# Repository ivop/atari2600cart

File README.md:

# atari2600cart
2K/4K Atari 2600 Cartridge PCB

Rescued my 2017 design from backup :)

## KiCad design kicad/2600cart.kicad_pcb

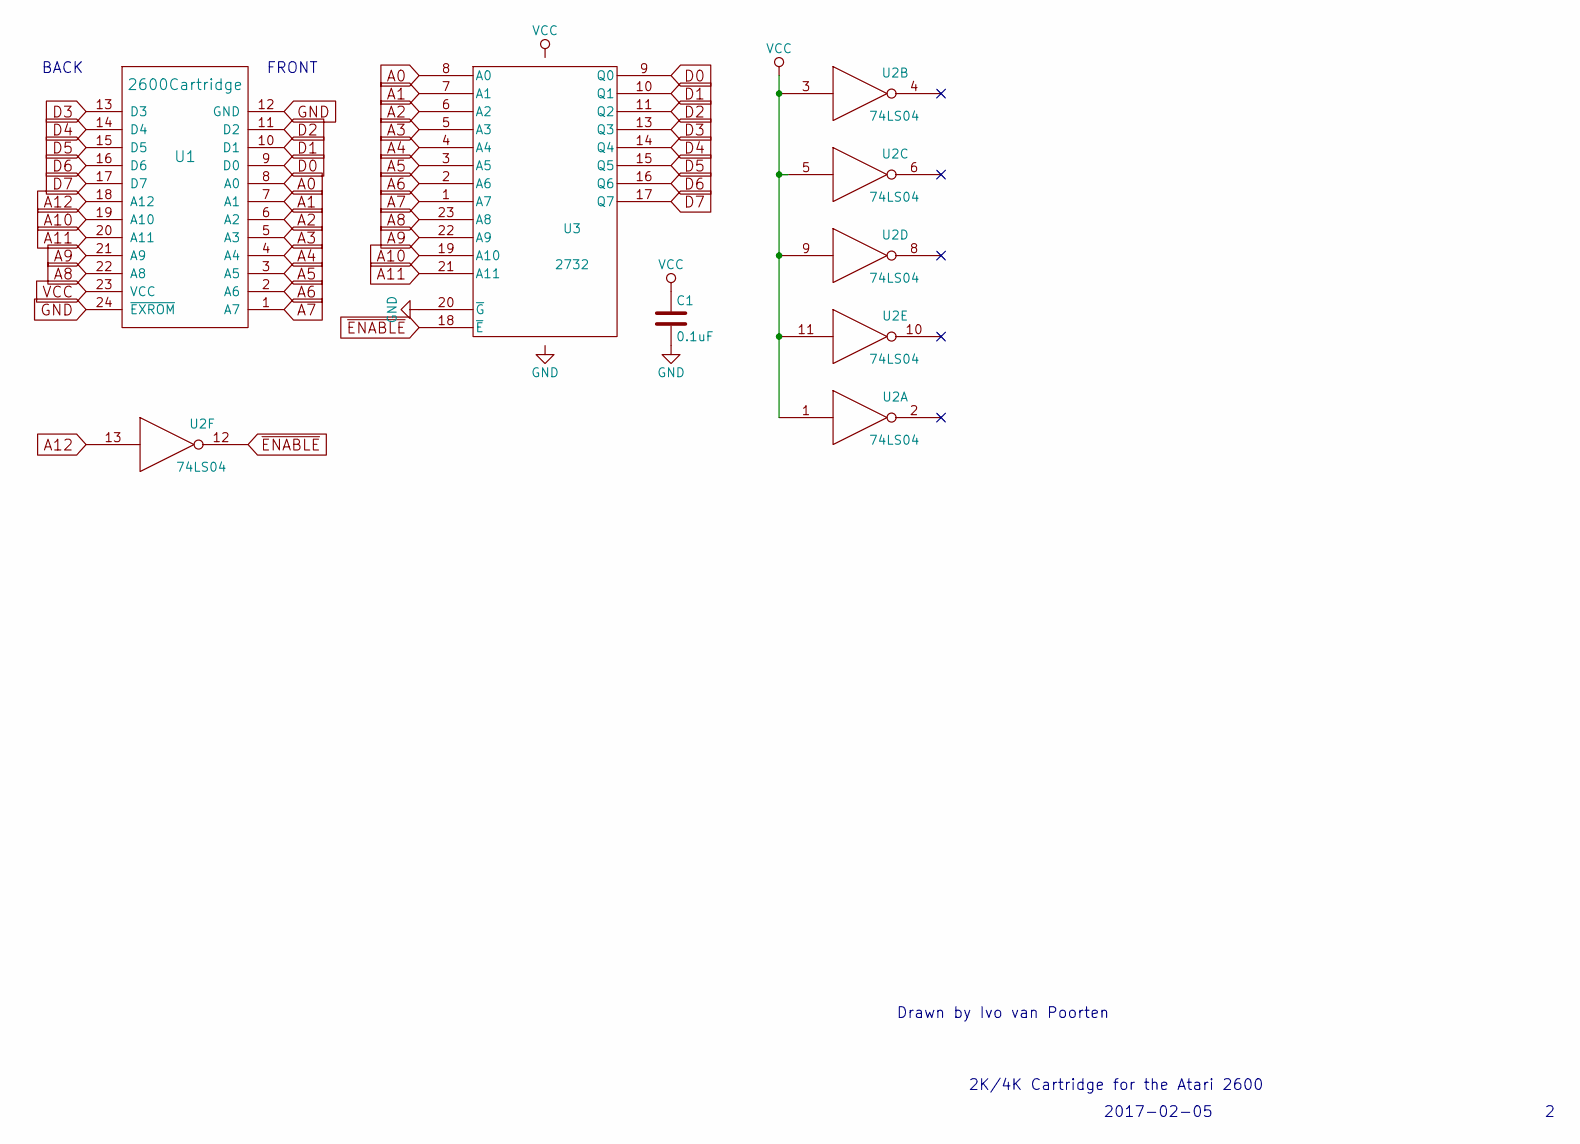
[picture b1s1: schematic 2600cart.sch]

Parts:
C1: 0.1uF; C_Disc_D3.0mm_W2.0mm_P2.50mm
U1: 2600Cartridge; 2600CART
U2: 74LS04; DIP-14_W7.62mm
U3: 2732; DIP-24_W15.24mm

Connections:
A0: U1.8 (A0), U3.8 (A0)
A1: U1.7 (A1), U3.7 (A1)
A2: U1.6 (A2), U3.6 (A2)
A3: U1.5 (A3), U3.5 (A3)
A4: U1.4 (A4), U3.4 (A4)
A5: U1.3 (A5), U3.3 (A5)
A6: U1.2 (A6), U3.2 (A6)
A7: U1.1 (A7), U3.1 (A7)
A8: U1.22 (A8), U3.23 (A8)
A9: U1.21 (A9), U3.22 (A9)
A10: U1.19 (A10), U3.19 (A10)
A11: U1.20 (A11), U3.21 (A11)
A12: U1.18 (A12), U2.13
D0: U1.9 (D0), U3.9 (Q0)
D1: U1.10 (D1), U3.10 (Q1)
D2: U1.11 (D2), U3.11 (Q2)
D3: U1.13 (D3), U3.13 (Q3)
D4: U1.14 (D4), U3.14 (Q4)
D5: U1.15 (D5), U3.15 (Q5)
D6: U1.16 (D6), U3.16 (Q6)
D7: U1.17 (D7), U3.17 (Q7)
GND: C1.2, U1.12 (GND), U1.24 (~EXROM), U2.7 (GND), U3.12 (GND), U3.20 (~G)
VCC: C1.1, U1.23 (VCC), U2.1, U2.3, U2.5, U2.9, U2.11, U2.14 (VCC), U3.24 (Vcc)
~ENABLE: U2.12, U3.18 (~E)

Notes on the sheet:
2K/4K Cartridge for the Atari 2600
2017-02-05
Drawn by Ivo van Poorten
FRONT
BACK

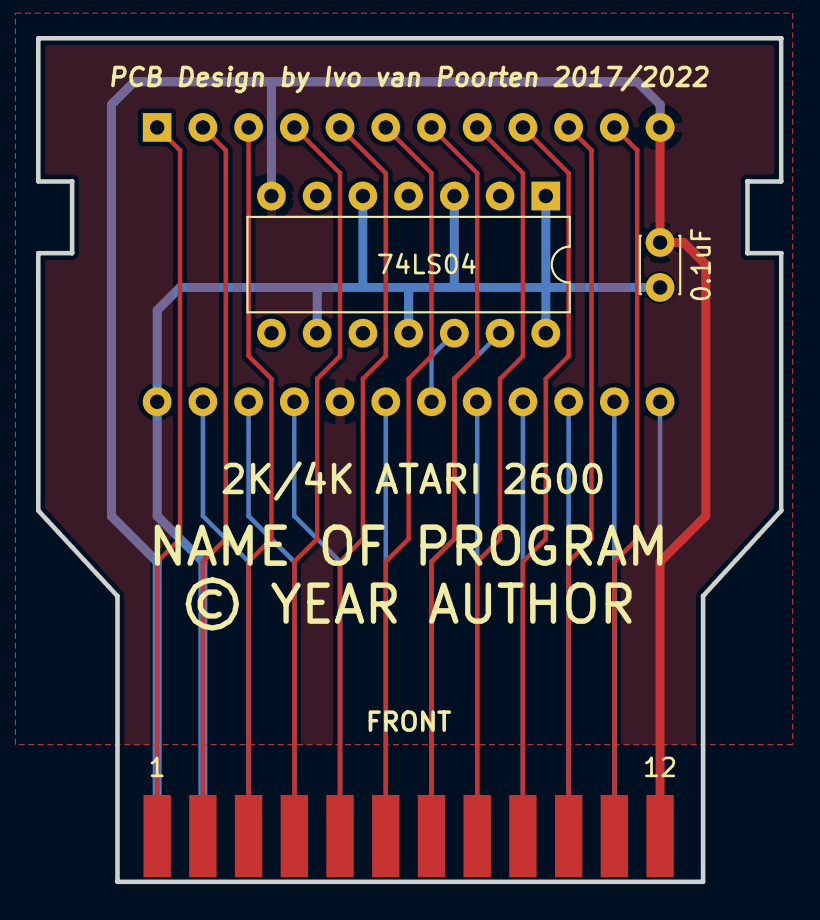
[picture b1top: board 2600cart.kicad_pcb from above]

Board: 2 copper layers, 41.3 x 46.9 mm, 4 parts (1 on the bottom side), 24 nets.

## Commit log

2022-09-21 new ignore paterns
2022-09-21 new ignore patterns
2022-09-21 generate generic gerbers
2022-09-21 add drill file
2022-09-21 fix schematic for new KiCad version, export netlist, import netlist, and run DRC
2022-09-21 load new netlist in combined outline+cart project
2022-09-21 unhide B silk (very irritating that this stored everytime)
2022-09-21 new gerbers from updated project
2022-09-21 remove useless track and via in combined project. it has now zero vias :)
    also
    don't track fp-info-cache anymore
2022-09-21 remove rescue backup
2022-09-21 MERGE all three project files
    The schematic and netlist now directly map to the full cartridge PCB
2022-09-21 upgrade to new footprints and restore 3D rendering
2022-09-21 new images
2022-09-21 Show all images
2022-09-21 remove cache cruft
2022-09-22 fix input/output for address lines
2022-09-22 remoce dcm
2022-09-22 ignore lib bck files
2022-09-22 remove attic files
2025-06-27 Add cache lib
2025-06-30 Add new gerbers, no name/author/year, exported with JLCPCB settings

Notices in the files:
kicad/2600cart.kicad_pcb:
© YEAR AUTHOR
